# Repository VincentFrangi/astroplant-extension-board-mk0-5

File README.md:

# Astroplant Extension Board MK0.5

## About This Project

AstoPlant Prototype Board Mk0.5

## Renderings

### Top

### Bottom

---

This project is managed and available on

You can view it [here](https://aisler.net/p/JYMRADDY). Start your own Powerful Prototype on [here](https://aisler.net).

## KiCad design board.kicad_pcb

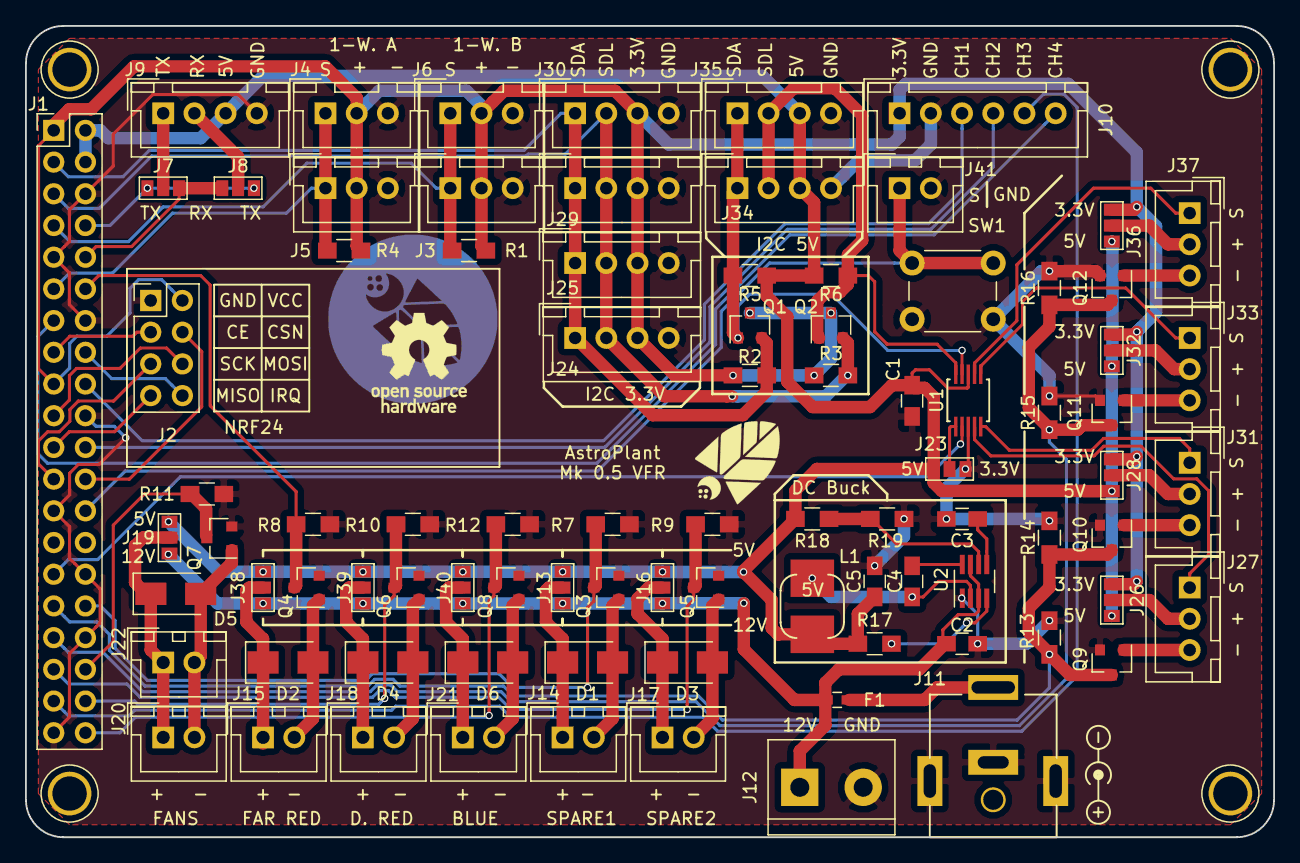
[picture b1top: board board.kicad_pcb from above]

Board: 2 copper layers, 100.0 x 65.0 mm, 88 parts (0 on the bottom side), 65 nets.

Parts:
C1, C4: 0.1uF; C_0805_HandSoldering
C2: 22uF; C_0805_HandSoldering
C3: 8.2nF; C_0805_HandSoldering
C5: 47uUF; C_0805_HandSoldering
D1, D2, D3, D4, D5, D6: S1A; D_SMA
F1: PRG18BC4R7MM1RB; C_0603_HandSoldering
J1: RPi_2/3_GPIO header; Pin_Header_Straight_2x20_Pitch2.54mm
J2: Conn_02x04_Odd_Even; Pin_Header_Straight_2x04_Pitch2.54mm
J3, J4, J5, J6, J27, J31, J33, J37: JST-XH_3; JST_XH_B03B-XH-A_03x2.50mm_Straight
J7, J8, J13, J16, J19, J23, J26, J28, J32, J36, J38, J39, J40: GS3
J9: JST_XH_UART; JST_XH_B04B-XH-A_04x2.50mm_Straight
J10: JST_XH_Relays; JST_XH_B06B-XH-A_06x2.50mm_Straight
J11: Jack-DC; PJ-063AH
J12: Conn_01x02; TerminalBlock_bornier-2_P5.08mm
J14, J15, J17, J18, J20, J21, J22, J41: JST_HX_2; JST_XH_B02B-XH-A_02x2.50mm_Straight
J24, J25, J29, J30, J34, J35: JST_XH_I2C; JST_XH_B04B-XH-A_04x2.50mm_Straight
L1: 3.3uH; 74437349033
Q1, Q2, Q3, Q4, Q5, Q6, Q7, Q8, Q9, Q10, Q11, Q12: IRLML6344TRPBF; SOT-23
R1, R2, R3, R4, R5, R6, R19: 10K; R_0805_HandSoldering
R7, R8, R9, R10, R11, R12, R13, R14, R15, R16, R17: 100K; R_0805_HandSoldering
R18: 59K; R_0805_HandSoldering
SW1: SW_Push; SW_PUSH_6mm
U1: ADS1015; ADS1015IDGST
U2: TPS563210DDF; SOT-23-8_Handsoldering

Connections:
+3V3: J1.1, J1.17, J2.2, J3.2, J4.2, J5.2, J6.2, J10.1, J24.3, J25.3, J26.1, J28.1, J29.3, J30.3, J32.1, J36.1, Q1.3, Q2.3, R1.1, R2.1, R3.1, R4.1
+5V: C1.1, C5.1, J1.2, J1.4, J9.3, J13.3, J16.3, J19.3, J23.1, J26.3, J28.3, J32.3, J34.3, J35.3, J36.3, J38.3, J39.3, J40.3, L1.2, R5.1, R6.1, R17.1, R18.1, U1.8
+12V: C2.1, F1.2, J12.1, J13.1, J16.1, J19.1, J38.1, J39.1, J40.1, U2.3, U2.7
AI0: J27.1, U1.4
AI1: J31.1, U1.5
AI2: J33.1, U1.6
AI3: J37.1, U1.7
CE0: J1.24, J2.4
GND: C1.2, C2.2, C3.2, C5.2, J1.6, J1.9, J1.14, J1.20, J1.25, J1.30, J1.34, J1.39, J2.1, J3.3, J4.3, J5.3, J6.3, J9.4, J10.2, J11.2, J11.3, J12.2, J23.3, J24.4, J25.4, J29.4, J30.4, J34.4, J35.4, J41.2, Q3.2, Q4.2, Q5.2, Q6.2, Q7.2, Q8.2, Q9.2, Q10.2, Q11.2, Q12.2, R7.2, R8.2, R9.2, R10.2, R11.2, R12.2, R13.2, R14.2, R15.2, R16.2, R19.2, SW1.2, U1.3, U2.1
GPIO4: J1.7, J3.1, J6.1, R1.2
GPIO5: J1.29, U1.2
GPIO6: J1.31, Q9.3, Q10.3, R13.1, R14.1
GPIO7: J1.26, J41.1, SW1.1
GPIO12: J1.32, Q3.3, R7.1
GPIO13: J1.33, Q11.3, Q12.3, R15.1, R16.1
GPIO16: J1.36, Q7.3, R11.1
GPIO17: J1.11, J4.1, J5.1, R4.2
GPIO18: J1.12, Q4.3, R8.1
GPIO19: J1.35, Q5.3, R9.1
GPIO20: J1.38, Q6.3, R10.1
GPIO21: J1.40, Q8.3, R12.1
GPIO22: J1.15, J2.3
GPIO23: J1.16, J2.8
GPIO24: J1.18, J10.3
GPIO25: J1.22, J10.4
GPIO26: J1.37, J10.5
GPIO27: J1.13, J10.6
MISO: J1.21, J2.7
MOSI: J1.19, J2.6
unnamed: C3.1, U2.5
unnamed: C4.1, U2.8
unnamed: C4.2, L1.1, U2.2
unnamed: D1.1, J13.2, J14.1
unnamed: D1.2, J14.2, Q3.1
unnamed: D2.1, J15.1, J38.2
unnamed: D2.2, J15.2, Q4.1
unnamed: D3.1, J16.2, J17.1
unnamed: D3.2, J17.2, Q5.1
unnamed: D4.1, J18.1, J39.2
unnamed: D4.2, J18.2, Q6.1
unnamed: D5.1, J19.2, J20.1, J22.1
unnamed: D5.2, J20.2, J22.2, Q7.1
unnamed: D6.1, J21.1, J40.2
unnamed: D6.2, J21.2, Q8.1
unnamed: F1.1, J11.1
unnamed: J7.2, J9.1
unnamed: J8.2, J9.2
unnamed: J23.2, U1.1
unnamed: J26.2, J27.2
unnamed: J27.3, Q9.1
unnamed: J28.2, J31.2
unnamed: J31.3, Q10.1
unnamed: J32.2, J33.2
unnamed: J33.3, Q11.1
unnamed: J36.2, J37.2
unnamed: J37.3, Q12.1
unnamed: R17.2, U2.4
unnamed: R18.2, R19.1, U2.6
RX: J1.10, J7.3, J8.3
SCL: J1.5, J24.2, J25.2, J29.2, J30.2, Q2.2, R3.2
SCLK: J1.23, J2.5
SCL_5V: J34.2, J35.2, Q2.1, R6.2, U1.10
SDA: J1.3, J24.1, J25.1, J29.1, J30.1, Q1.2, R2.2
SDA_5V: J34.1, J35.1, Q1.1, R5.2, U1.9
TX: J1.8, J7.1, J8.1

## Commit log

2018-09-21 Syncing AISLER project with GitHub repository
2018-12-20 Add schematics

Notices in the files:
parts and their libraries:
Copyright 2016 Accelerated Designs. All rights reserved.
